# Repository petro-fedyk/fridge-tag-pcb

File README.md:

# Fridge Tag PCB

A compact IoT device for monitoring temperature and humidity inside refrigerators with wireless connectivity.

## Overview

The Fridge Tag is a battery-powered sensor device designed to monitor environmental conditions inside refrigerators. It features:

- 🌡️ Temperature monitoring (-40°C to +80°C)
- 💧 Humidity monitoring (0-100% RH)
- 📡 WiFi and Bluetooth Low Energy connectivity
- 🔋 Long battery life (3-6 months on CR2032)
- 📦 Compact form factor (50mm x 30mm)

## Repository Structure

```
fridge-tag-pcb/
├── hardware/              # PCB design files
│   ├── fridge-tag.kicad_pro      # KiCad project file
│   ├── fridge-tag.kicad_pcb      # PCB layout
│   ├── fridge-tag.kicad_sch      # Schematic
│   ├── gerbers/                   # Gerber files for manufacturing
│   ├── libraries/                 # Custom component libraries
│   ├── pcb/                       # PCB-related files
│   └── schematic/                 # Schematic-related files
├── docs/                  # Documentation
│   ├── BOM.md                     # Bill of Materials
│   ├── design-spec.md             # Design specifications
│   └── assembly-instructions.md   # Assembly guide
├── fabrication/           # Manufacturing files
│   └── manufacturing-spec.md      # Fab specifications
└── README.md             # This file
```

## Key Components

- **ESP32-WROOM-32**: Main microcontroller with WiFi/BLE
- **DHT22**: Temperature and humidity sensor
- **CR2032**: Coin cell battery (220mAh)
- **SMD Components**: 0805 size resistors and capacitors

## Getting Started

### Prerequisites

- **KiCad 6.0+**: For viewing and editing PCB files
- **Gerber Viewer**: For reviewing manufacturing files (optional)

### Opening the Project

1. Clone this repository:
   ```bash
   git clone https://github.com/petro-fedyk/fridge-tag-pcb.git
   cd fridge-tag-pcb
   ```

2. Open KiCad and load the project:
   ```
   File → Open Project → hardware/fridge-tag.kicad_pro
   ```

3. View the schematic:
   ```
   Open Schematic Editor (Eeschema)
   ```

4. View the PCB layout:
   ```
   Open PCB Editor (Pcbnew)
   ```

## Documentation

- **[Bill of Materials](docs/BOM.md)**: Complete list of components
- **[Design Specification](docs/design-spec.md)**: Technical specifications and architecture
- **[Assembly Instructions](docs/assembly-instructions.md)**: Step-by-step assembly guide
- **[Manufacturing Spec](fabrication/manufacturing-spec.md)**: PCB fabrication requirements

## PCB Specifications

| Parameter | Value |
|-----------|-------|
| Board Size | 50mm x 30mm |
| Layers | 2 (Top/Bottom) |
| Thickness | 1.6mm |
| Copper Weight | 1 oz (35μm) |
| Surface Finish | ENIG |
| Solder Mask | Green |
| Min Track/Space | 0.2mm/0.2mm |

## Manufacturing

### Generating Gerber Files

1. Open the PCB in KiCad Pcbnew
2. File → Plot
3. Select required layers
4. Generate Gerber and drill files
5. Review in Gerber viewer
6. Zip files for manufacturer

### Recommended Manufacturers

- JLCPCB
- PCBWay
- OSH Park
- Seeed Studio

## Assembly

The board can be assembled using:
- **SMT Assembly**: Recommended for production quantities
- **Hand Soldering**: Suitable for prototypes (0805 components are hand-solderable)

See [Assembly Instructions](docs/assembly-instructions.md) for detailed steps.

## Firmware

The PCB is designed to work with ESP32 firmware. Recommended frameworks:
- **Arduino IDE**: Easy to get started
- **ESP-IDF**: Full featured development
- **PlatformIO**: Modern build system

Example firmware features:
- Deep sleep mode for power saving
- Periodic sensor readings (configurable interval)
- BLE advertising or WiFi data transmission
- OTA firmware updates

## Testing

After assembly:
1. Visual inspection
2. Continuity testing
3. Power-on test
4. Sensor functionality test
5. Wireless connectivity test
6. Battery life measurement

## Power Consumption

| Mode | Current | Duration |
|------|---------|----------|
| Deep Sleep | ~10μA | 95% of time |
| Sensor Read | ~20mA | 2 seconds |
| WiFi Transmit | ~80mA | 3 seconds |
| BLE Advertise | ~40mA | 1 second |

**Estimated Battery Life**: 3-6 months with readings every 5 minutes

## License

This project is open source. See LICENSE file for details.

## Contributing

Contributions are welcome! Please:
1. Fork the repository
2. Create a feature branch
3. Make your changes
4. Submit a pull request

## Version History

- **v1.0** (Current): Initial design
  - ESP32-based design
  - DHT22 sensor integration
  - CR2032 battery power
  - 2-layer PCB

## Support

For issues, questions, or suggestions:
- Open an issue on GitHub
- Check existing documentation
- Review the schematic and PCB layout

## Acknowledgments

- ESP32 community for excellent documentation
- KiCad project for the amazing EDA tool
- Component manufacturers for datasheets

## Disclaimer

This is a prototype design. Use at your own risk. Always verify the design before manufacturing.

---

**Status**: Design Phase  
**Last Updated**: 2025-10-26  
**Maintainer**: petro-fedyk

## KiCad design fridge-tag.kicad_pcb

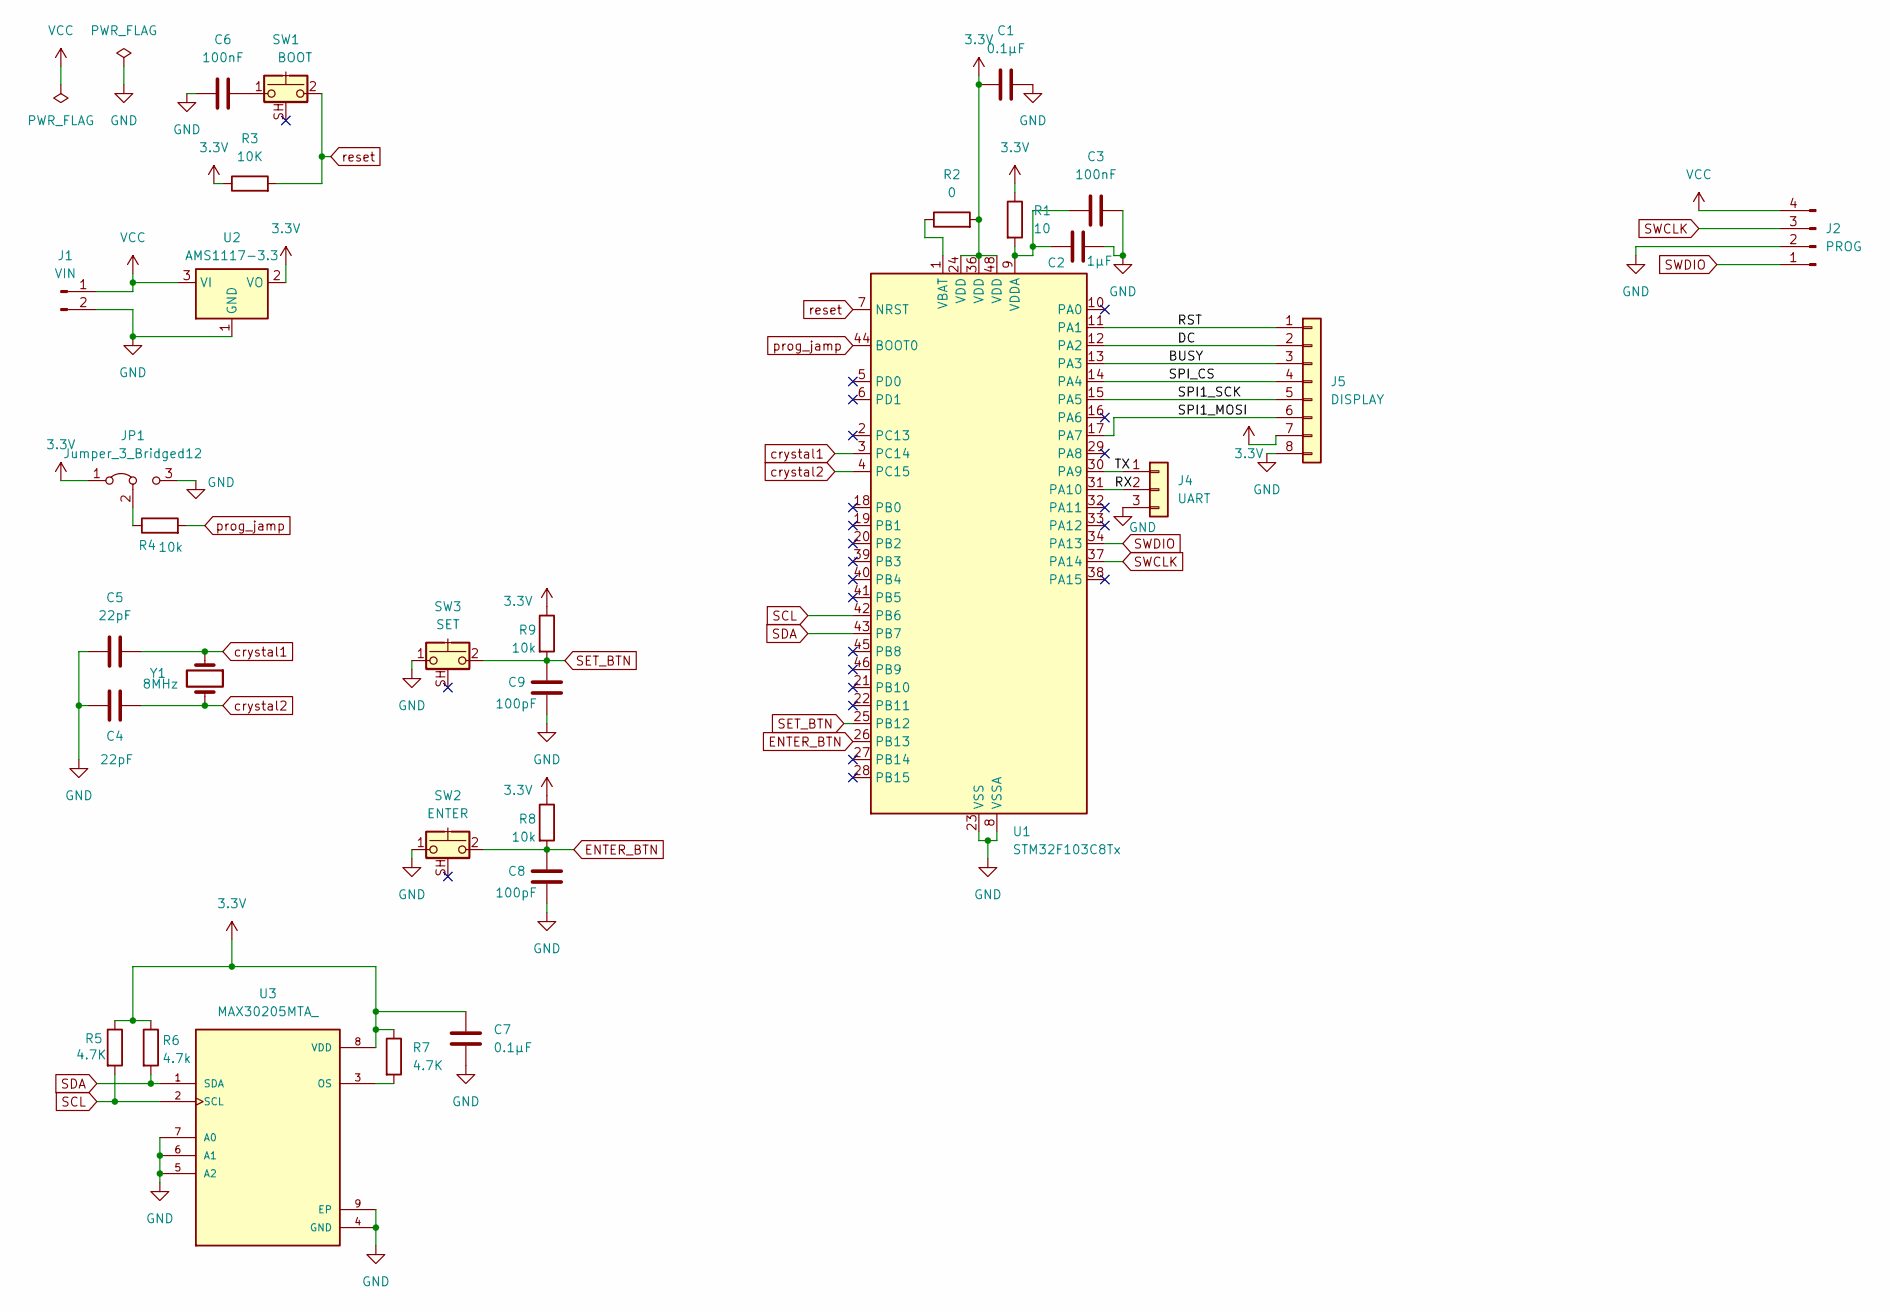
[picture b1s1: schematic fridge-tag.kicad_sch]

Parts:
C1, C7: 0.1µF; L_1206_3216Metric_Pad1.22x1.90mm_HandSolder
C2: 1µF; L_1206_3216Metric_Pad1.22x1.90mm_HandSolder
C3: 100nF; L_1206_3216Metric_Pad1.22x1.90mm_HandSolder
C4, C5: 22pF; L_1206_3216Metric_Pad1.22x1.90mm_HandSolder
C6: 100nF; C_1206_3216Metric_Pad1.33x1.80mm_HandSolder
C8, C9: 100pF; L_1206_3216Metric_Pad1.22x1.90mm_HandSolder
J1: VIN; JWT_A3963_1x02_P3.96mm_Vertical
J2: PROG
J4: UART; FanPinHeader_1x03_P2.54mm_Vertical
J5: DISPLAY; Hirose_DF13-08P-1.25DSA_1x08_P1.25mm_Vertical
JP1: Jumper_3_Bridged12; PhoenixContact_GMSTBVA_2,5_3-G_1x03_P7.50mm_Vertical
R1: 10; L_1206_3216Metric_Pad1.22x1.90mm_HandSolder
R2: 0; L_1206_3216Metric_Pad1.22x1.90mm_HandSolder
R3: 10K; L_1206_3216Metric_Pad1.22x1.90mm_HandSolder
R4, R8, R9: 10k; L_1206_3216Metric_Pad1.22x1.90mm_HandSolder
R5, R7: 4.7K; L_1206_3216Metric_Pad1.22x1.90mm_HandSolder
R6: 4.7k; L_1206_3216Metric_Pad1.22x1.90mm_HandSolder
SW1: BOOT; SW_SPST_PTS647_Sx70
SW2: ENTER; SW_SPST_PTS647_Sx70
SW3: SET; SW_SPST_PTS647_Sx70
U1: STM32F103C8Tx; LQFP-48_7x7mm_P0.5mm
U2: AMS1117-3.3; SOT-323_SC-70
U3: MAX30205MTA_; SON65P300X300X80-9N
Y1: 8MHz; Crystal_DS10_D1.0mm_L4.3mm_Vertical

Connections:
3.3V: C1.1, C7.1, J5.7, JP1.1 (A), R1.1, R2.2, R3.1, R5.1, R6.1, R7.1, R8.1, R9.1, U1.24 (VDD), U1.36 (VDD), U1.48 (VDD), U2.2 (VO), U3.8 (VDD)
/BUSY: J5.3, U1.13 (PA3)
/DC: J5.2, U1.12 (PA2)
/RST: J5.1, U1.11 (PA1)
/RX: J4.2, U1.31 (PA10)
/SPI1_MOSI: J5.6, U1.17 (PA7)
/SPI1_SCK: J5.5, U1.15 (PA5)
/SPI_CS: J5.4, U1.14 (PA4)
/TX: J4.1, U1.30 (PA9)
ENTER_BTN: C8.1, R8.2, SW2.2, U1.26 (PB13)
GND: C1.2, C2.2, C3.2, C4.1, C5.1, C6.1, C7.2, C8.2, C9.2, J1.2, J2.2, J4.3, J5.8, JP1.3 (B), SW2.1, SW3.1, U1.8 (VSSA), U1.23 (VSS), U1.35 (VSS), U1.47 (VSS), U2.1 (GND), U3.4 (GND), U3.5 (A2), U3.6 (A1), U3.7 (A0), U3.9 (EP)
unnamed: C6.2, SW1.1
unnamed: JP1.2 (C), R4.1
unnamed: R2.1, U1.1 (VBAT)
unnamed: C2.1, C3.1, R1.2, U1.9 (VDDA)
unnamed: R7.2, U3.3 (OS)
SCL: R5.2, U1.42 (PB6), U3.2 (SCL)
SDA: R6.2, U1.43 (PB7), U3.1 (SDA)
SET_BTN: C9.1, R9.2, SW3.2, U1.25 (PB12)
SWCLK: J2.3, U1.37 (PA14)
SWDIO: J2.1, U1.34 (PA13)
VCC: J1.1, J2.4, U2.3 (VI)
crystal1: C5.2, U1.3 (PC14), Y1.1
crystal2: C4.2, U1.4 (PC15), Y1.2
prog_jamp: R4.2, U1.44 (BOOT0)
reset: R3.2, SW1.2, U1.7 (NRST)

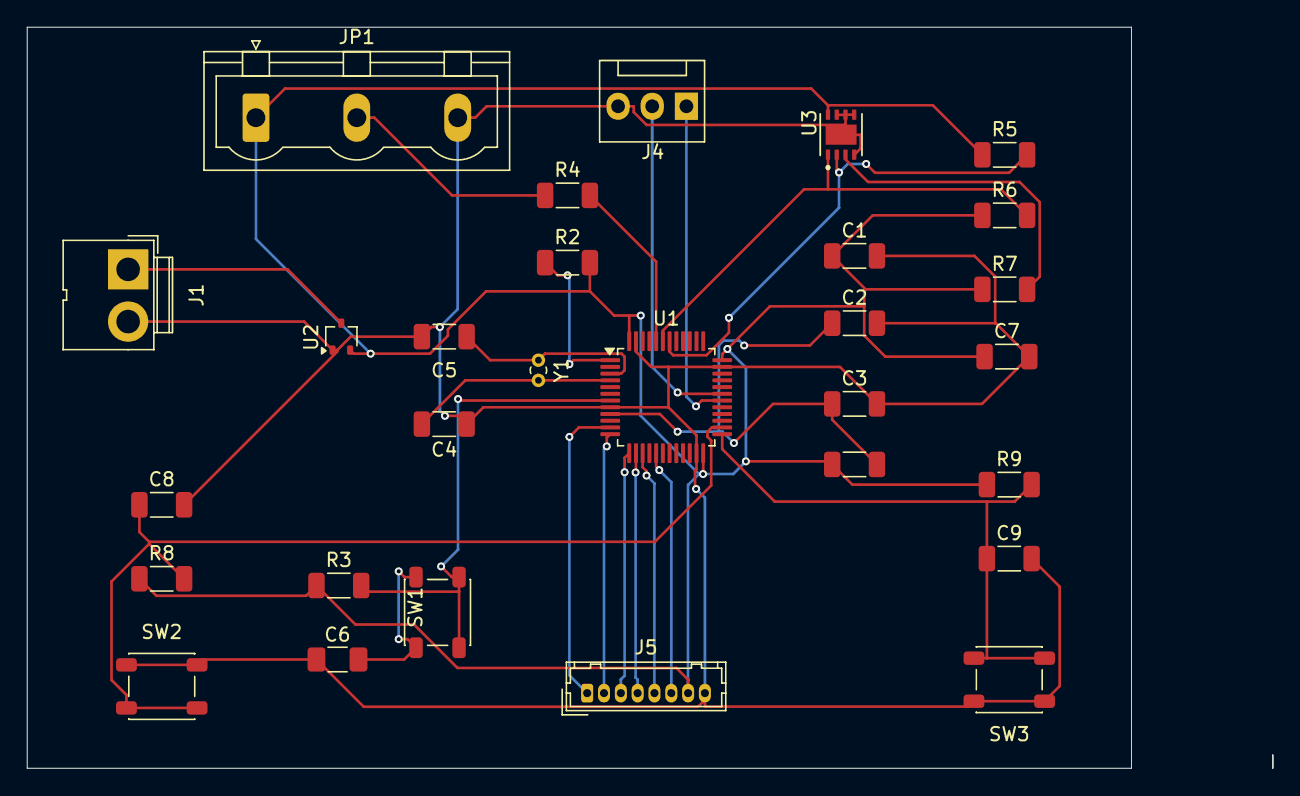
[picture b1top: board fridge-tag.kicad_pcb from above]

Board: 2 copper layers, 92.6 x 55.1 mm, 29 parts (0 on the bottom side), 24 nets.

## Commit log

2025-10-26 Initial plan
2025-10-26 Update README with project description
    Add description for custom PCB design.
2025-10-26 Complete PCB design structure for fridge tag with comprehensive documentation
2025-10-26 Add project status tracking document

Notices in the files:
README.md:
License: MIT
